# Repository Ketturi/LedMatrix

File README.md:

# LedMatrix
128x10 LED matrix IoT display.

ESP8266 WiFi module controls daisychained 32x10 led display units.

## Hardware

Custom build enclosure to hold four display modules, their interlinking cables, power busbars and controller board together. Acrylic parts are lasercut from dxf images designed in Autodesk Fusion360.
[3D CAD Model in A360](http://a360.co/1Sen1dj).

[Control board](https://github.com/Ketturi/LedMatrix/tree/master/Hardware/ControlPCB) for connectinc ESP8266 module to display modules is designed in eagle and is made by milling it with CNC routter. 
Display modules are connected to ESP8266 with high speed SPI for matrix column data, and 4 parallel lines for matrix row address.

Display modules used in this single prototype are propriety, and do not contain make or model. There is no other available information of these, and all work here is done trough reverse engineering.
Code and control board is easily adaptable to publicly obtainable LED matrix displays.

## Software
ESP8266 module runs arduino sketch. Arduino IDE needs [Board core files](https://github.com/esp8266/Arduino) to be able to compile software for module.
Use the arduino.org IDE 1.7.9! Arduino.cc IDE is not working due issues with arduino-builder. You need to install board files and libraries manually.

Simple function converts binary bitmap data to column data corresponding selected row and column. Data is then transferred trough SPI to column led drivers (32 bit shift register in each module daisychained together)
Row is selected trough 4-bit address. 

### ESP8266 spesific features
#### OTA Update
Software incorporates [OTA updates](http://esp8266.github.io/Arduino/versions/2.1.0/doc/ota_updates/ota_updates.html) through Arduino IDE. When ESP8266 is connected to same network as computer containing IDE, board shows in port menu.
#### WiFi Manager
ESP8266 uses [WiFi Manager](https://github.com/tzapu/WiFiManager) library that allows modifying wlan credentials and other settings without recompiling and uploading the software.
When control board is powered, it tries to connect previously saved WiFi access point. If that however fails, ESP8266 creates access point itself. By connecting this access point user can go to http://192.168.4.1 address and input their own WiFi credentials.
Credentials are saved to flash, and ESP8266 tries to connect that access point. After successful connection display is initialized and starts to show data.
### Arduino IDE board settings

| Setting | Option | Explanaition |
| --- | --- |  --- | 
| Board | Generic ESP8266 Module |Install board from http://github.com/esp8266/Arduino
| Flash Mode | QIO |Selects how flash is controlled, QIO = 4 data lines
| Flash Size | 4M (1M SPIFFS) |4MB flash IC, 1M file system (3MB for scetch&OTA)
| Debug port | Disabled |Disables serial debug, serial lines used for data lines
| Debug level | None |No debuging
| Reset Method | ck |Does not matter, no serial programming reset ability
| Flash Frequency | 40Mhz |Probably 40Mhz, 80Mhz should be carefully tested
| Upload Using | OTA |Updated over network
| CPU Frequency | 160Mhz |Speed boost for faster display
| Upload SPEED | 115200| Does not matter when using OTA
| Port | FoxMatrix at <ip> (Generic ESP8266 Module) |Select device from network, shows only when properly connected and discovered

###Kukkaconvert
Kukkaconvert.exe is small windows command line utility for converting PNG images to bitmap binary data for display.
"kukkaconvert.exe image.png" accepts 12 pixel high png black and white images and outputs binary data to output.txt file.

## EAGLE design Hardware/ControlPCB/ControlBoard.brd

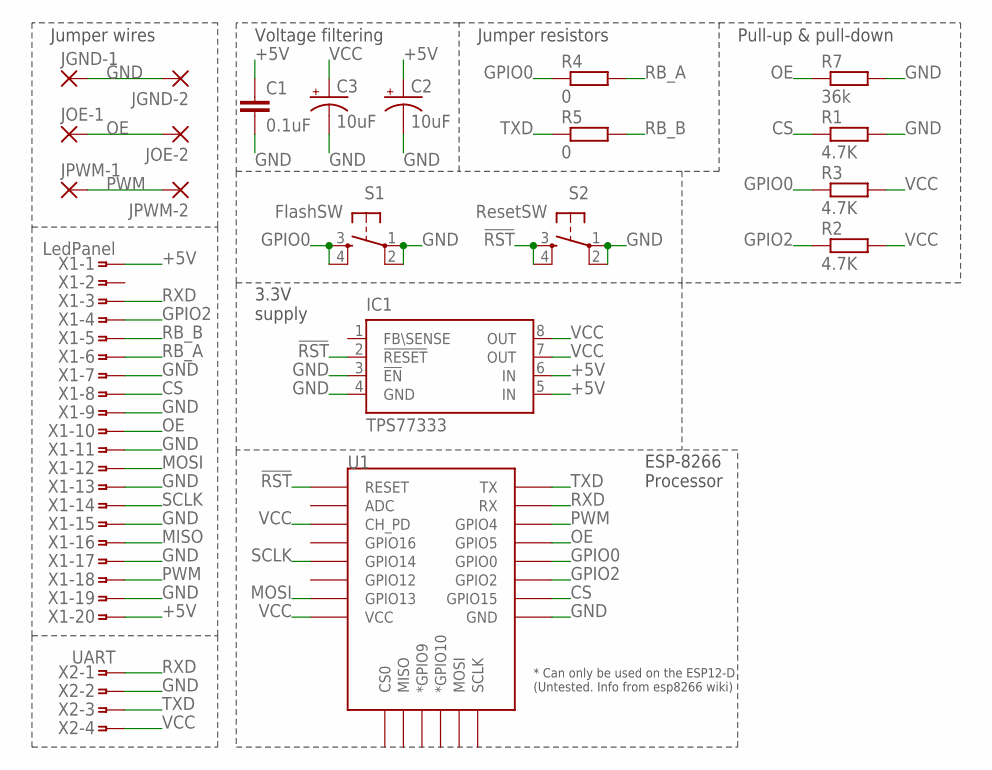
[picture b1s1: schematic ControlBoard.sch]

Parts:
C1: 0.1uF; 0603-CAP
C2, C3: 10uF; EIA3528
IC1: TPS77333; SOP-08
JGND-1, JGND-2: SMD2; SMD1,27-2,54
JOE-1, JOE-2: SMD2; SMD1,27-2,54
JPWM-1, JPWM-2: SMD2; SMD1,27-2,54
R1, R2, R3: 4.7K; R1206
R4, R5: 0; R5025W
R7: 36k; M2012
S1: FlashSW; DTSM-6
S2: ResetSW; DTSM-6
U1: ESP12ESMD; ESP12E-SMD
X1: LedPanel; SMDTOP20
X2: UART; SMDTOP4

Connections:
!RST: IC1.2 (!RESET), S2.3, S2.4, U1.RESET
+5V: C1.1, C2.A (+), IC1.5 (IN), IC1.6 (IN), X1.1, X1.20
CS: R1.1, U1.GPIO15, X1.8
GND: C1.2, C2.C (-), C3.C (-), IC1.3 (!EN), IC1.4 (GND), JGND-1.1, JGND-2.1, R1.2, R7.2, S1.1, S1.2, S2.1, S2.2, U1.GND, X1.7, X1.9, X1.11, X1.13, X1.15, X1.17, X1.19, X2.2
GPIO0: R3.1, R4.1, S1.3, S1.4, U1.GPIO0
GPIO2: R2.1, U1.GPIO2, X1.4
MISO: X1.16
MOSI: U1.GPIO13, X1.12
OE: JOE-1.1, JOE-2.1, R7.1, U1.GPIO5, X1.10
PWM: JPWM-1.1, JPWM-2.1, U1.GPIO4, X1.18
RB_A: R4.2, X1.6
RB_B: R5.2, X1.5
RXD: U1.RXD0 (RX), X1.3, X2.1
SCLK: U1.GPIO14, X1.14
TXD: R5.1, U1.TXD0 (TX), X2.3
VCC: C3.A (+), IC1.7 (OUT), IC1.8 (OUT), R2.2, R3.2, U1.CH_PD, U1.VCC, X2.4

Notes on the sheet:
Jumper wires
Voltage filtering
Jumper resistors
Pull-up & pull-down
3.3V supply
ESP-8266 Processor

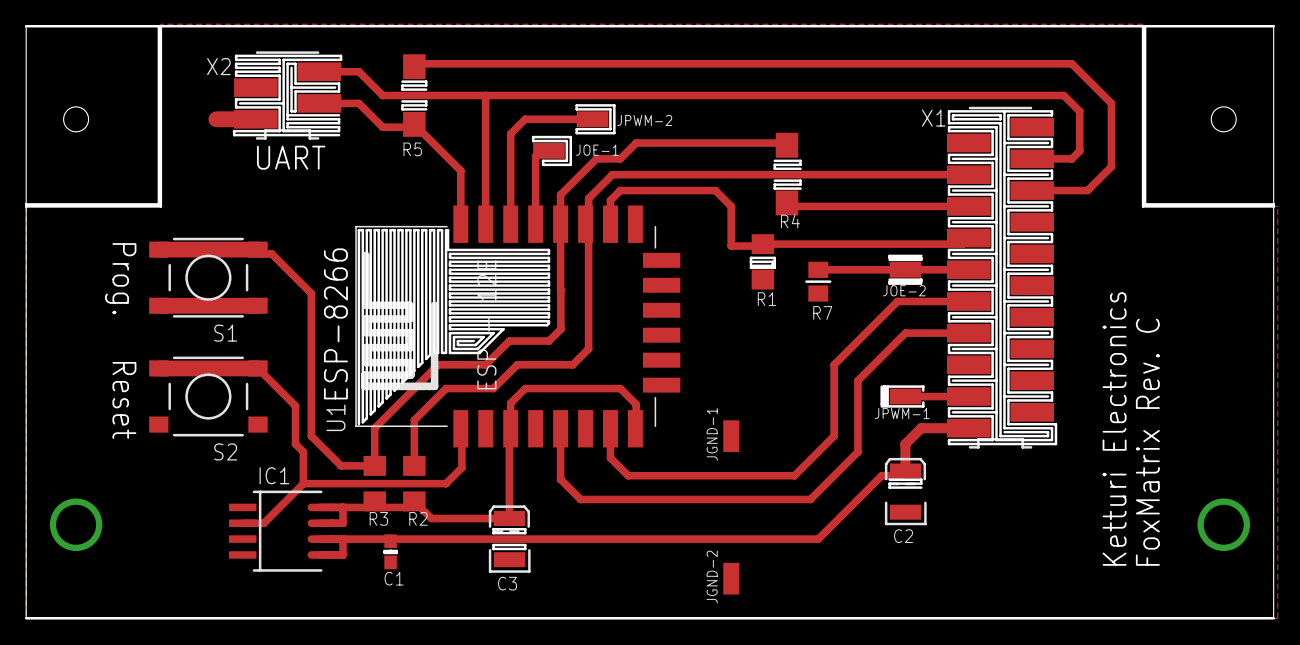
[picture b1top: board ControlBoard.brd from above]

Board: 2 copper layers, 100.0 x 47.5 mm, 21 parts (0 on the bottom side), 15 nets.

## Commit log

2016-02-03 :tada: Added .gitattributes
2016-02-03 First test arduino scetch
2016-02-03 Crude bitmap functionality
2016-02-03 Better bitmap functinality with animation and scrolling
2016-02-03 Tampere hacklab 32x12 scroller
2016-02-05 Misc files
2016-02-05 some font stuff
2016-02-17 Faster SPI implementation
2016-02-17 CodeCleaning
2016-02-17 Font stuff
2016-02-18 More fonts ant bitmaps
2016-02-18 Code changes
    Target changed from *duino nano to pro micro
2016-03-05 Target changed to ESP8266
    Target MCU is now ESP8266 wifi enabled chip. Eagle board files and
    schematic for cnc routed prototype board and updated arduino code that
    compiles for ESP8266.
2016-03-22 Some PCB changes
2016-03-24 Updated schematics and pcb
    Cleaned up schematics and new board layout with milling code files.
2016-03-24 Included WiFiManager
    If wifi AP is not found, esp goes to AP mode and serves user config page
    for setting up wifi.
2016-03-25 Added documentation
    Better comments in source code. Schematic and board layout as images.
2016-04-05 Yet more code documentation
2016-04-15 Images of hardware
2016-04-18 Dirty Fix for arduino builder bug
    Had to flip whole structure upside down because this piece of ****:
    https://github.com/arduino/arduino-builder/issues/68
    https://github.com/arduino/arduino-builder/issues/80
    https://github.com/arduino/arduino-builder/issues/85 and countless other
    issue tickets, arduino builder preprocessor fails to do prototype and
    can't reorder functions so everything must be just in the right order
2016-04-21 More bitmaps and arduino scetch
    Added some nice bitmaps for demostration. Included arduino scetch that
    WORKS with arduino.ORG IDE 1.7.9!
    Use arduino.org's version of IDE, as arduino.cc's IDE is broken and sad.
2016-04-29 PlatformIO as IDE
2017-03-03 Moving to Adafruit_GFX library and dynamic display framebuffer
    Rewrote whole code, now in FoxMatrix class that can be used as library
    for driwing display. Added Adafruit_GFX library support and implemented
    memory mapped framebuffer with option for double buffering.
2017-06-04 Implemented NTP time display and crude TKL bus time table display
    Updates include very crude TKL bus stop monitor library and method to
    get NTP time. Also includes new fonts, new bitmaps and some other
    improvements.
2017-06-04 Added time conversion TKL BusStop library

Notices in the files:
parts and their libraries:
SparkFun-Capacitors: Licensing: Creative Commons ShareAlike 4.0 International - https://creativecommons.org/licenses/by-sa/4.0
